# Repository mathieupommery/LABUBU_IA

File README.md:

# LABUBU IA

## Hardware

###  Specs
- ESP32-S3
- MEMS Micro ICS-43434
- Amplifier Max 98357
- Built-in LTC4065 lipo charger 
- Built-in 1s lipo and micro sd card
- WIFI/BLE antenna connector
- Push button for application purpose
- connector for external on/off switch, external USB, external speaker and adressable led.

###  PCB
- 4 layers under 900mm2

### Some view 

### 3D pcb case 

##  Software

### Audio_Player 
- Scan button at startup: if pressed goes into msc mode and expose sd card on usb to add new song (sd in spi mode too extremely slow)
- After that scan all the .wav in the memory
- then if you short press : toggle the play state of the current song
- if you long press : play the next song in alphabetical order.

### IA_assistant

-in progress 

## Result 

Picture of the pcb ( cable on top are soldered because i had not the jst ghs 8pin in stock )

View of the pcb with the 1s 150mah lipo battery connected

View of the External power switch (on one side battery is disconnected from ldo and usb is connected to ldo and on other side usb is disconnected from ldo and battery is connected ) 
and view of the usb port both are hidden in the labubu's feet.

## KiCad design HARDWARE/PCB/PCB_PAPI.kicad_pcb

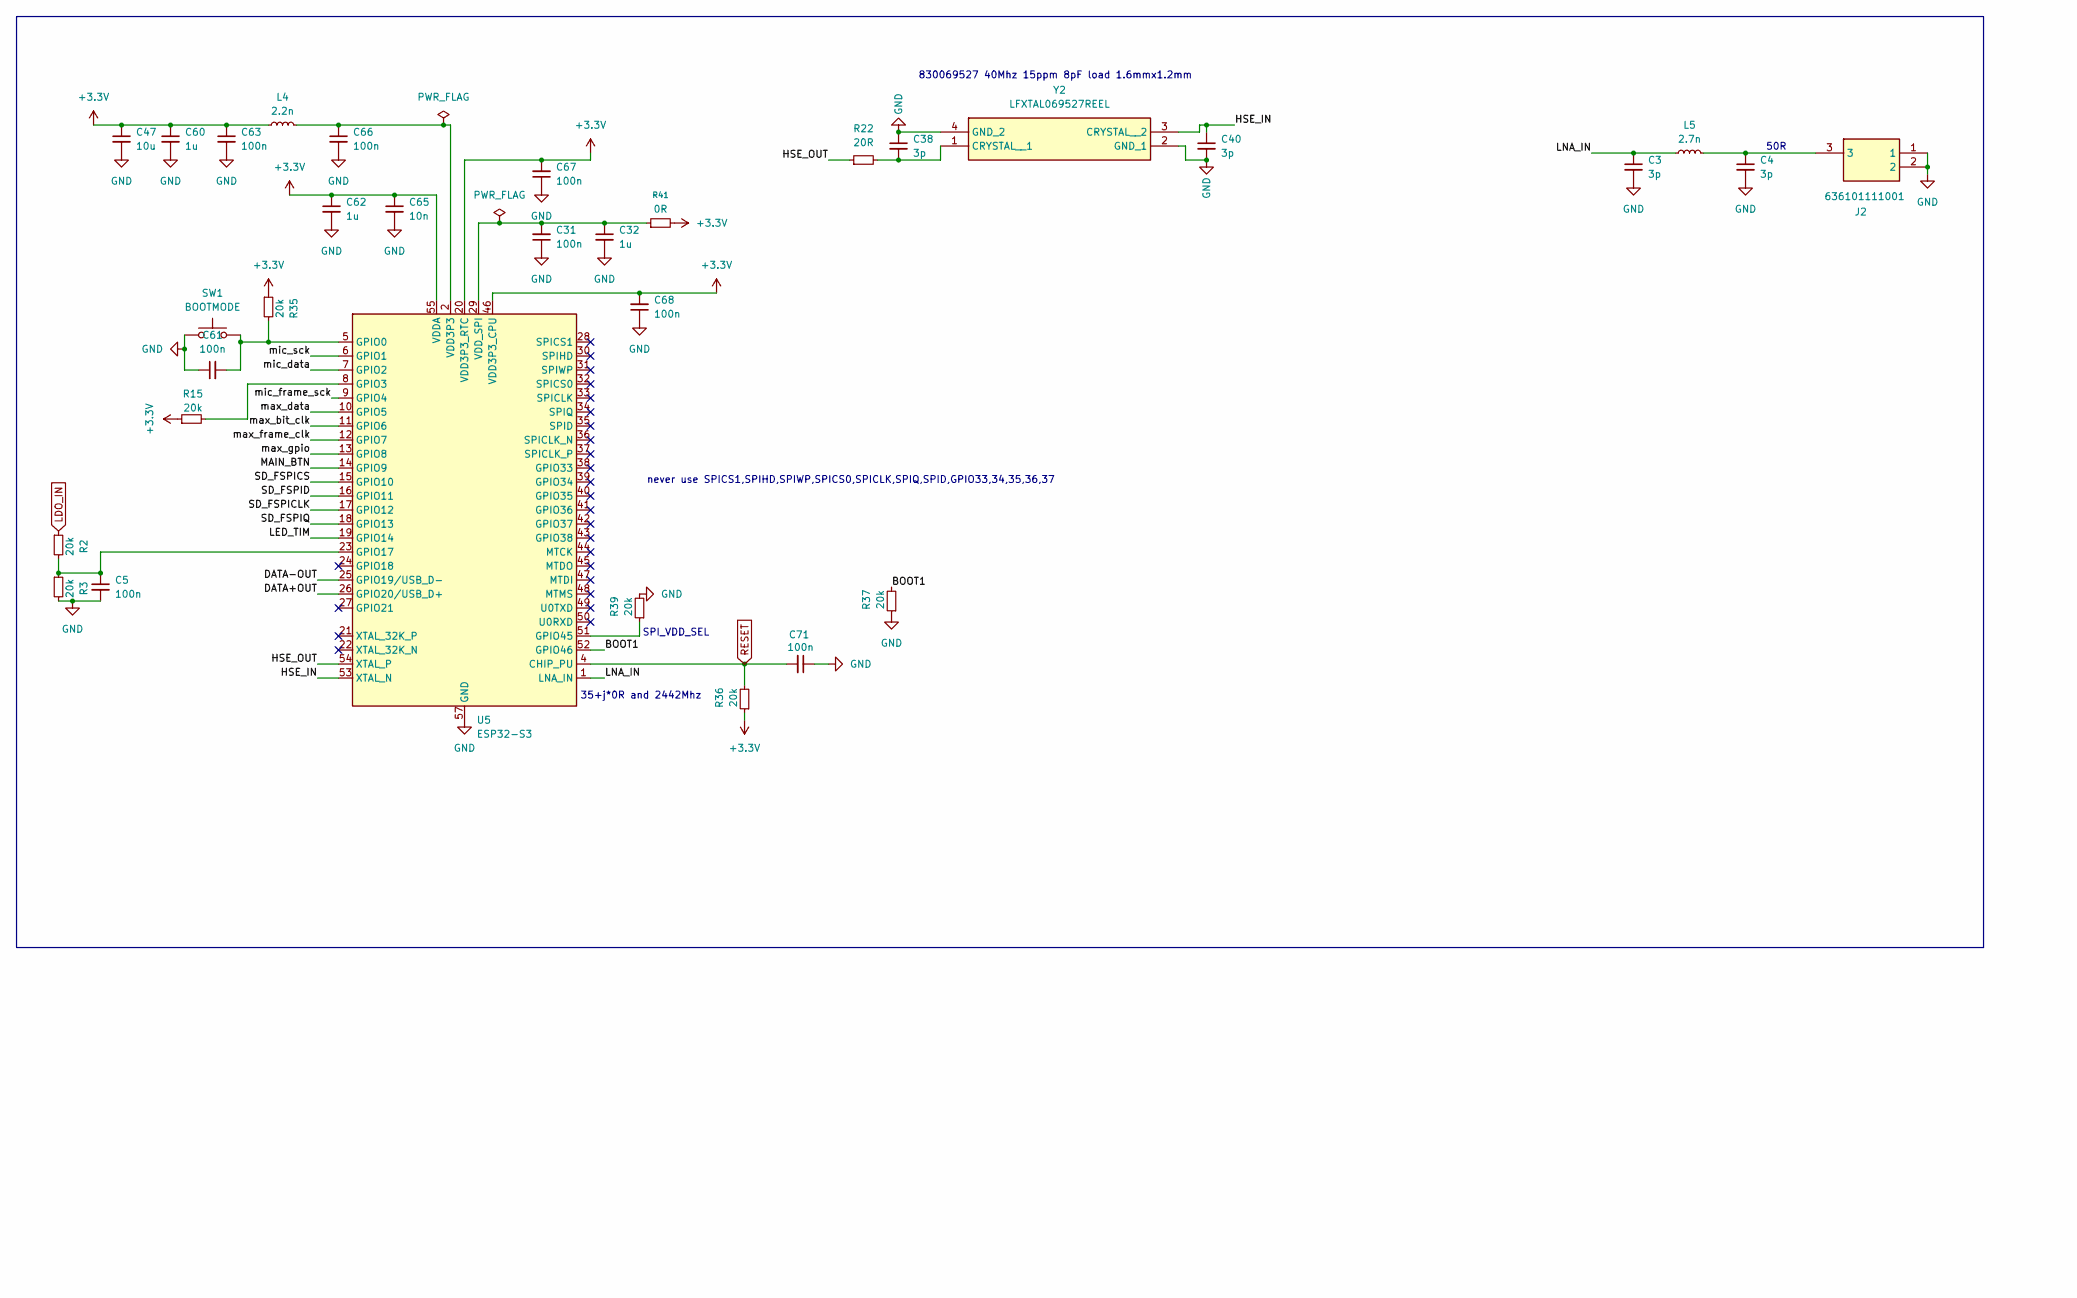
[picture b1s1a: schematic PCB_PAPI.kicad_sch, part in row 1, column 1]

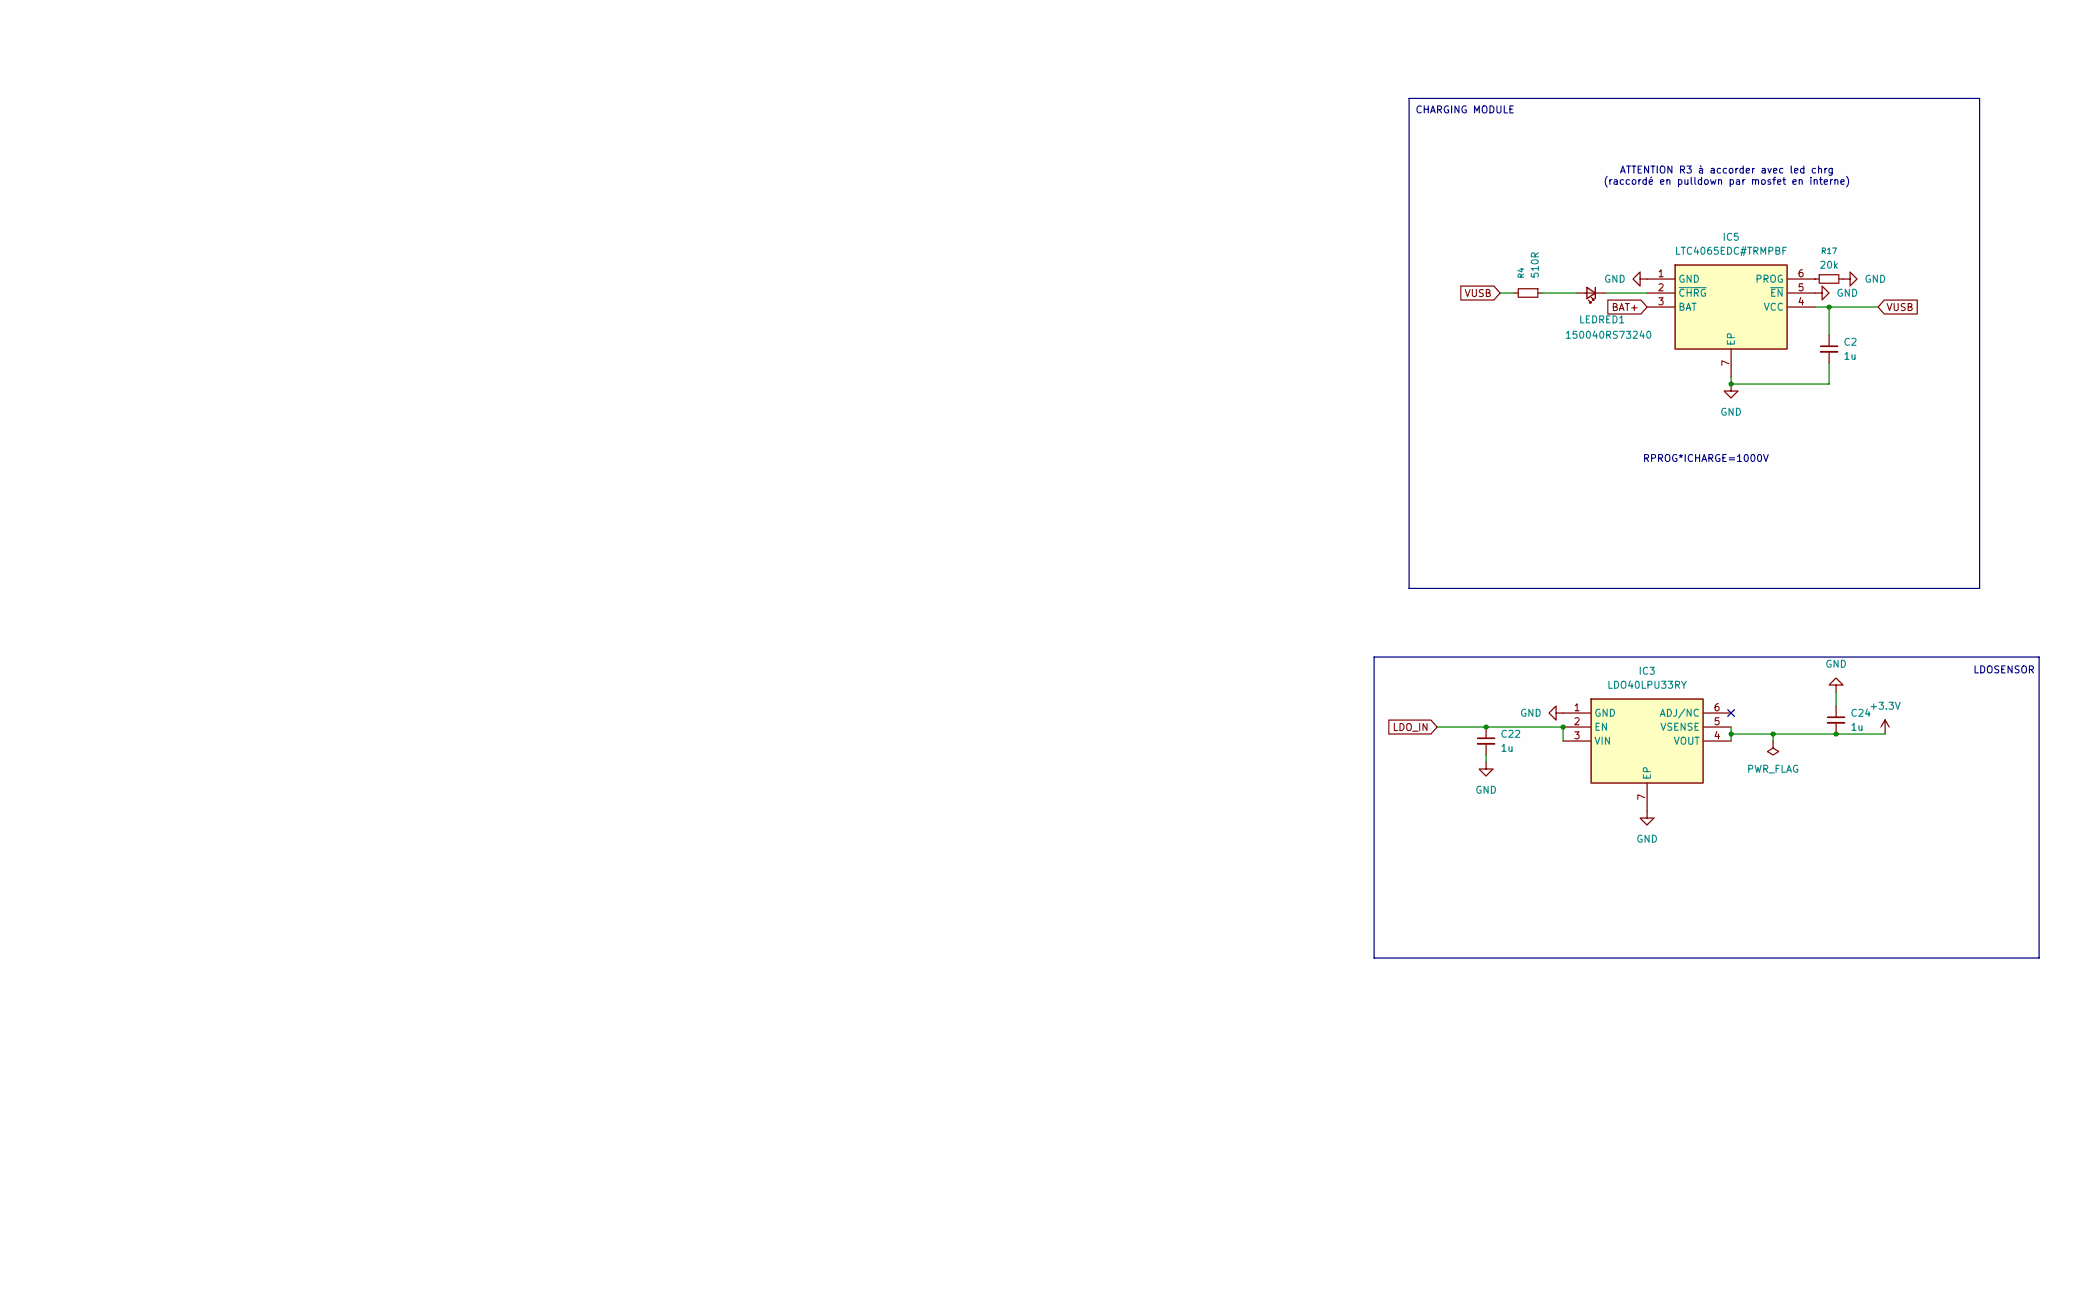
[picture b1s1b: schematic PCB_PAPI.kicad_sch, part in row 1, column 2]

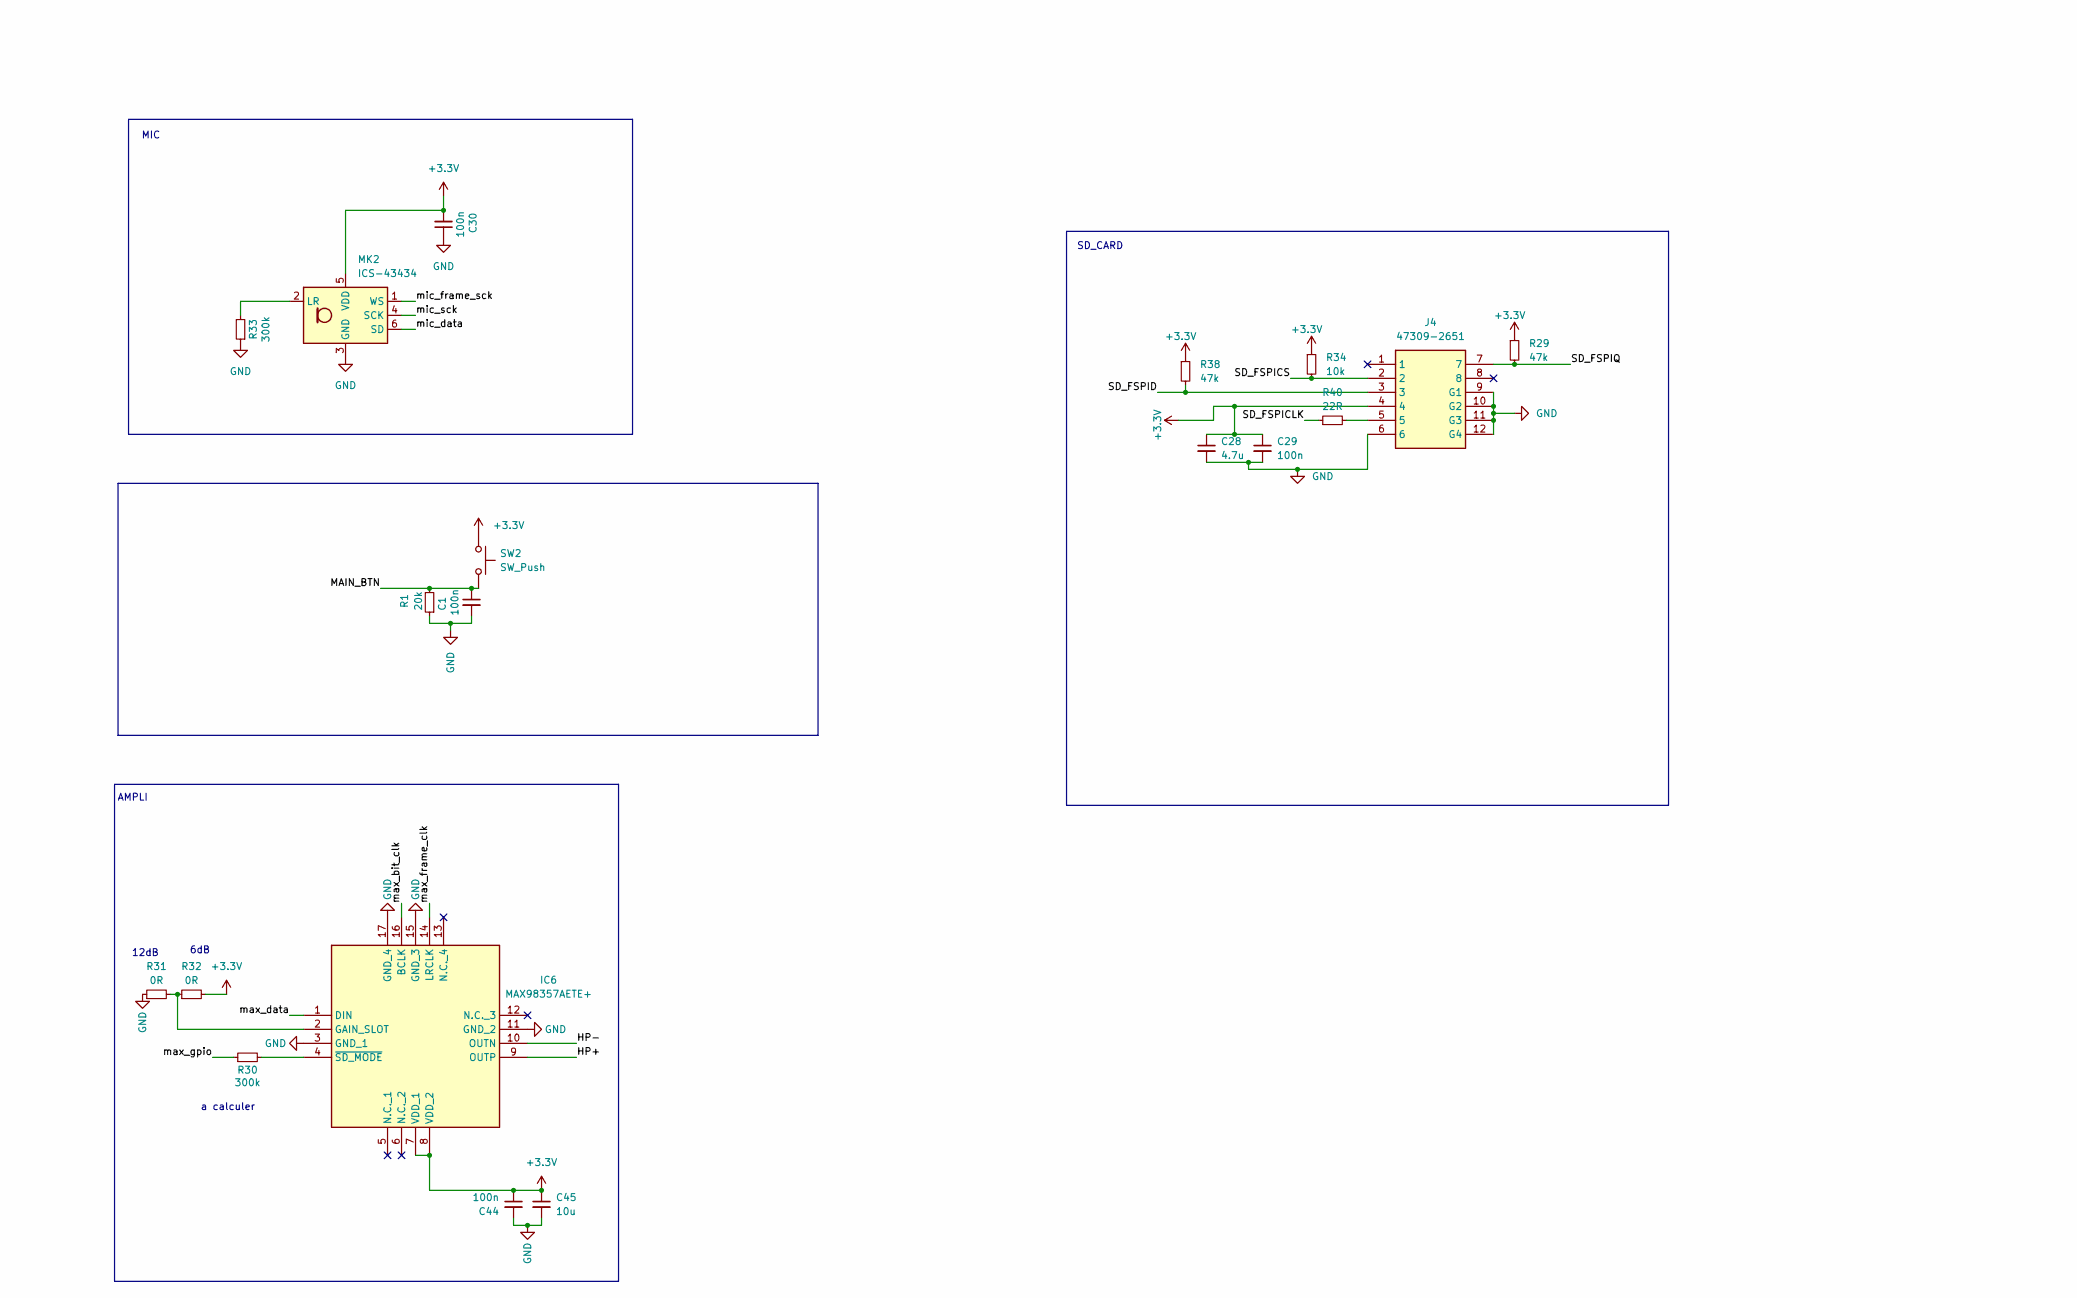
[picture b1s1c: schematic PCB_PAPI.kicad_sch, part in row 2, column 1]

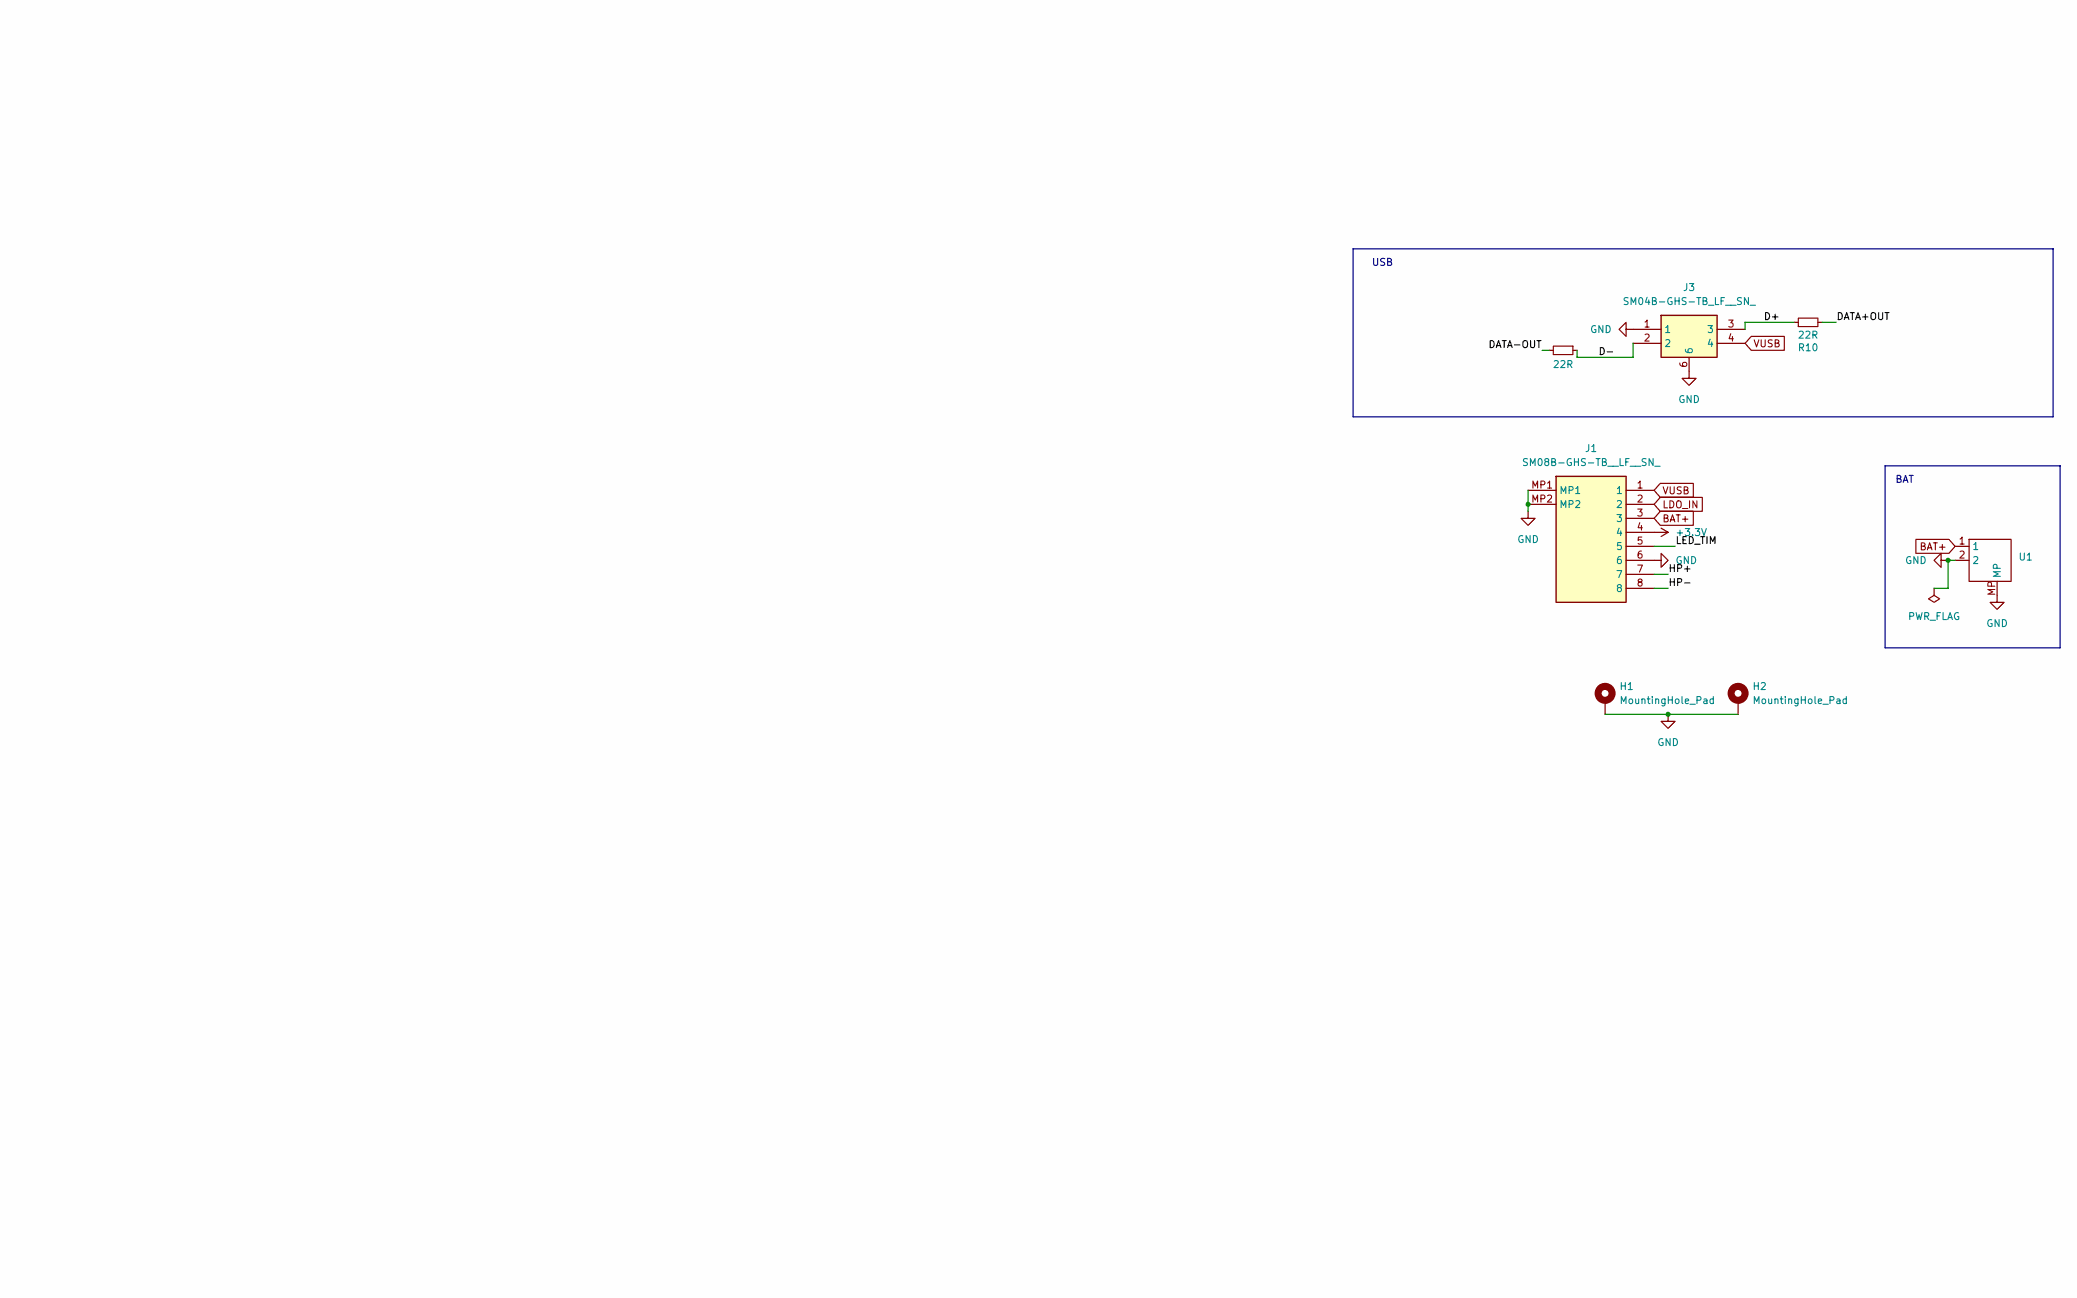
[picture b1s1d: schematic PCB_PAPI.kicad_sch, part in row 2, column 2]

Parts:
C1, C5, C30, C31, C61, C63, C66, C67, C68, C71: 100n; C_0201_0603Metric_Pad0.64x0.40mm_HandSolder
C2: 1u; C_0402_1005Metric
C3, C4, C38, C40: 3p; C_0201_custom
C22, C24: 1u; C_0402_1005Metric; Manufacturer_Part_Number 885012105012; Mouser Part Number 710-885012105012
C28: 4.7u; C_0402_1005Metric_Pad0.74x0.62mm_HandSolder
C29, C44: 100n; C_0201_0603Metric
C32, C60, C62: 1u; C_0402_1005Metric_Pad0.74x0.62mm_HandSolder
C45: 10u; C_0402_1005Metric; Manufacturer_Part_Number 885012105008; Mouser Part Number 710-885012105008
C47: 10u; C_0402_1005Metric_Pad0.74x0.62mm_HandSolder
C65: 10n; C_0201_0603Metric_Pad0.64x0.40mm_HandSolder
H1, H2: MountingHole_Pad; MountingHole_2.2mm_M2_Pad_Via
IC3: LDO40LPU33RY; SON95P300X300X90-7N-D; Manufacturer_Part_Number LDO40LPU33RY; Mouser Part Number 511-LDO40LPU33RY
IC5: LTC4065EDC#TRMPBF; SON50P200X200X80-7N-D; Manufacturer_Part_Number LTC4065EDC#TRMPBF; Mouser Part Number 584-LTC4065EDCTRMPBF
IC6: MAX98357AETE+; QFN50P300X300X80-17N; Manufacturer_Part_Number MAX98357AETE+; Mouser Part Number 700-MAX98357AETE+
J1: SM08B-GHS-TB__LF__SN_; SM08BGHSTBLFSN; Manufacturer_Part_Number SM08B-GHS-TB (LF)(SN)
J2: 636101111001; Mouser Part Number 710-636101111001
J3: SM04B-GHS-TB_LF__SN_; SM04B-GHS-TB; Manufacturer_Part_Number SM04B-GHS-TB(LF)(SN); Mouser Part Number N/A
J4: 47309-2651; 473092651; Manufacturer_Part_Number 47309-2651
L4: 2.2n; L_0603_1608Metric
L5: 2.7n; L_0603_1608Metric
LEDRED1: 150040RS73240; LED_0402_1005Metric; Manufacturer_Part_Number 150040GS73240; Mouser Part Number 710-150040GS73240
MK2: ICS-43434; InvenSense_ICS-43434-6_3.5x2.65mm
R1, R2, R3, R15, R35, R36, R37, R39: 20k; R_0201_0603Metric_Pad0.64x0.40mm_HandSolder
R4: 510R; R_0201_0603Metric_Pad0.64x0.40mm_HandSolder; Mouser Part Number 603-RC0201JR-07510RL
R9, R10: 22R; R_0201_0603Metric; Manufacturer_Part_Number ERJ-1GNF22R0C; Mouser Part Number 667-ERJ-1GNF22R0C
R17: 20k; R_0201_0603Metric_Pad0.64x0.40mm_HandSolder; Mouser Part Number 603-AC0201FR-0720KL
R22: 20R; R_0201_0603Metric
R29, R38: 47k; R_0201_0603Metric
R30, R33: 300k; R_0201_0603Metric; Manufacturer_Part_Number ERJ-1GNF1000C; Mouser Part Number 667-ERJ-1GNF1000C
R31: 0R; R_0201_custom; Manufacturer_Part_Number ERJ-1GNF1000C; Mouser Part Number 667-ERJ-1GNF1000C
R32: 0R; R_0201_0603Metric; Manufacturer_Part_Number ERJ-1GNF1000C; Mouser Part Number 667-ERJ-1GNF1000C
R34: 10k; R_0201_0603Metric
R40: 22R; R_0201_0603Metric
R41: 0R; R_0402_1005Metric_Pad0.72x0.64mm_HandSolder
SW1: BOOTMODE; KXT341LHS
SW2: SW_Push; SW_Push_1P1T_NO_CK_PTS125Sx85SMTR
U1: JST_SH_BM02B-SRSS-TB_1x02-1MP_P1.00mm_Vertical; Mouser Part Number 306-BM02BSRSSTBLFSNP
U5: ESP32-S3; QFN-56-1EP_7x7mm_P0.4mm_EP4x4mm
Y2: LFXTAL069527REEL; Manufacturer_Part_Number LFXTAL069527REEL

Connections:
+3.3V: C24.2, C28.1, C29.1, C30.2, C44.1, C45.1, C47.1, C60.1, C62.1, C63.1, C65.1, C67.2, C68.2, IC3.4 (VOUT), IC3.5 (VSENSE), IC6.7 (VDD_1), IC6.8 (VDD_2), J1.4, J4.4, L4.1, MK2.5 (VDD), R15.1, R29.1, R32.2, R34.1, R35.1, R36.1, R38.1, R41.2, SW2.1, U5.20 (VDD3P3_RTC), U5.46 (VDD3P3_CPU), U5.55 (VDDA), U5.56 (VDDA)
/BOOT1: R37.2, U5.52 (GPIO46)
/D+: J3.3, R10.1
/D-: J3.2, R9.1
/DATA+OUT: R10.2, U5.26 (GPIO20/USB_D+)
/DATA-OUT: R9.2, U5.25 (GPIO19/USB_D-)
/HP+: IC6.9 (OUTP), J1.7
/HP-: IC6.10 (OUTN), J1.8
/HSE_IN: C40.1, U5.53 (XTAL_N), Y2.3 (CRYSTAL__2)
/HSE_OUT: R22.1, U5.54 (XTAL_P)
/LED_TIM: J1.5, U5.19 (GPIO14)
/LNA_IN: C3.1, L5.1, U5.1 (LNA_IN)
/MAIN_BTN: C1.1, R1.2, SW2.2, U5.14 (GPIO9)
/SD_FSPICLK: R40.1, U5.17 (GPIO12)
/SD_FSPICS: J4.2, R34.2, U5.15 (GPIO10)
/SD_FSPID: J4.3, R38.2, U5.16 (GPIO11)
/SD_FSPIQ: J4.7, R29.2, U5.18 (GPIO13)
/max_bit_clk: IC6.16 (BCLK), U5.11 (GPIO6)
/max_data: IC6.1 (DIN), U5.10 (GPIO5)
/max_frame_clk: IC6.14 (LRCLK), U5.12 (GPIO7)
/max_gpio: R30.1, U5.13 (GPIO8)
/mic_data: MK2.6 (SD), U5.7 (GPIO2)
/mic_frame_sck: MK2.1 (WS), U5.9 (GPIO4)
/mic_sck: MK2.4 (SCK), U5.6 (GPIO1)
BAT+: IC5.3 (BAT), J1.3, U1.1
GND: C1.2, C2.2, C3.2, C4.2, C5.2, C22.2, C24.1, C28.2, C29.2, C30.1, C31.1, C32.2, C38.1, C40.2, C44.2, C45.2, C47.2, C60.2, C61.1, C62.2, C63.2, C65.2, C66.2, C67.1, C68.1, C71.1, H1.1, H2.1, IC3.1 (GND), IC3.7 (EP), IC5.1 (GND), IC5.5 (~EN), IC5.7 (EP), IC6.3 (GND_1), IC6.11 (GND_2), IC6.15 (GND_3), IC6.17 (GND_4), J1.6, J1.MP1, J1.MP2, J2.1, J2.2, J3.1, J3.5, J3.6, J4.6, J4.9 (G1), J4.10 (G2), J4.11 (G3), J4.12 (G4), MK2.3 (GND), R1.1, R3.2, R17.2, R31.1, R33.1, R37.1, R39.2, SW1.1, U1.2, U1.MP, U5.57 (GND), Y2.2 (GND_1), Y2.4 (GND_2)
LDO_IN: C22.1, IC3.2 (EN), IC3.3 (VIN), J1.2, R2.1
unnamed: C4.1, J2.3, L5.2
unnamed: C66.1, L4.2, U5.2 (VDD3P3), U5.3 (VDD3P3)
unnamed: IC5.6 (PROG), R17.1
unnamed: IC5.2 (~CHRG), LEDRED1.1 (K)
unnamed: IC6.2 (GAIN_SLOT), R31.2, R32.1
unnamed: IC6.4 (~SD_MODE), R30.2
unnamed: J4.5, R40.2
unnamed: LEDRED1.2 (A), R4.1
unnamed: MK2.2 (LR), R33.2
unnamed: C61.2, R35.2, SW1.2, U5.5 (GPIO0)
unnamed: R15.2, U5.8 (GPIO3)
unnamed: C5.1, R2.2, R3.1, U5.23 (GPIO17)
unnamed: R39.1, U5.51 (GPIO45)
unnamed: C31.2, C32.1, R41.1, U5.29 (VDD_SPI)
unnamed: C38.2, R22.2, Y2.1 (CRYSTAL__1)
RESET: C71.2, R36.2, U5.4 (CHIP_PU)
VUSB: C2.1, IC5.4 (VCC), J1.1, J3.4, R4.2

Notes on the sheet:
MIC
SPI_VDD_SEL
12dB
35+j*0R and 2442Mhz
SD_CARD
50R
a calculer
BAT
RPROG*ICHARGE=1000V
never use SPICS1,SPIHD,SPIWP,SPICS0,SPICLK,SPIQ,SPID,GPIO33,34,35,36,37
AMPLI
CHARGING MODULE
830069527 40Mhz 15ppm 8pF load 1.6mmx1.2mm
ATTENTION R3 à accorder avec led chrg (raccordé en pulldown par mosfet en interne)
6dB
USB
LDOSENSOR

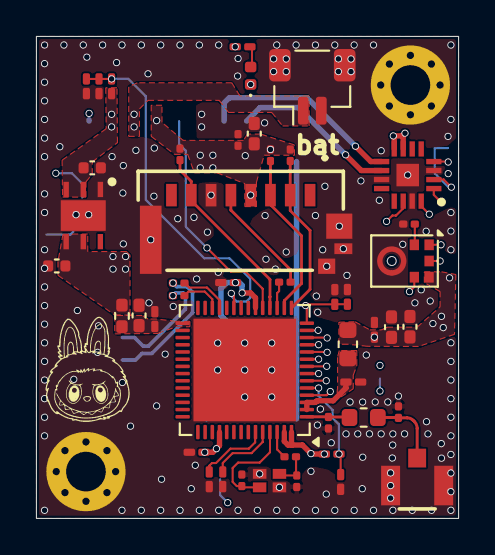
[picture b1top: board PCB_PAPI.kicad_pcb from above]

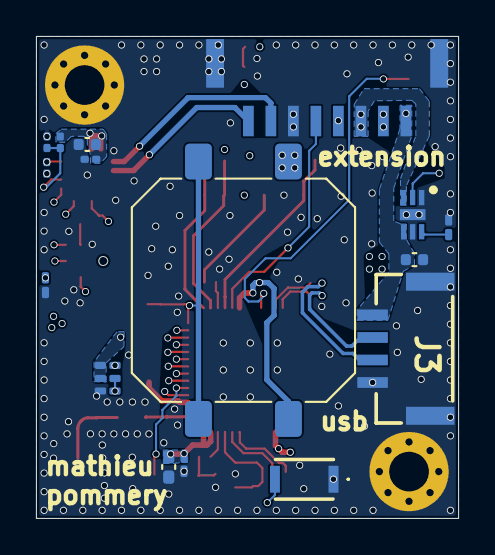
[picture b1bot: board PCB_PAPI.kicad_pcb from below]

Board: 4 copper layers, 23.4 x 26.8 mm, 66 parts (18 on the bottom side), 44 nets.

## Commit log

2026-01-12 Add README with project specifications and features
    Added detailed hardware and software specifications for the LABUBU IA project, including components, PCB details, images, and functionality of the audio player and AI assistant.
2026-01-12 Refactor images and headings in README.md
    Updated image formatting and alignment in the README.
2026-01-12 Update README with 3D PCB case images
    Added images for 3D PCB case and updated layout.
2026-01-12 Update README with PCB images and descriptions
    Added images and descriptions of PCB and components.
2026-01-12 Improve Audio_Player section in README.md
    Refined the description of the Audio_Player functionality for clarity.
